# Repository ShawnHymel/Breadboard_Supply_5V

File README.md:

Breadboard Supply 5V
====================

PCB design files for Custom PCB with EAGLE workshop. 

License Information
-------------------

Please review the LICENSE.md file for license information. 

Distributed as-is; no warranty is given.

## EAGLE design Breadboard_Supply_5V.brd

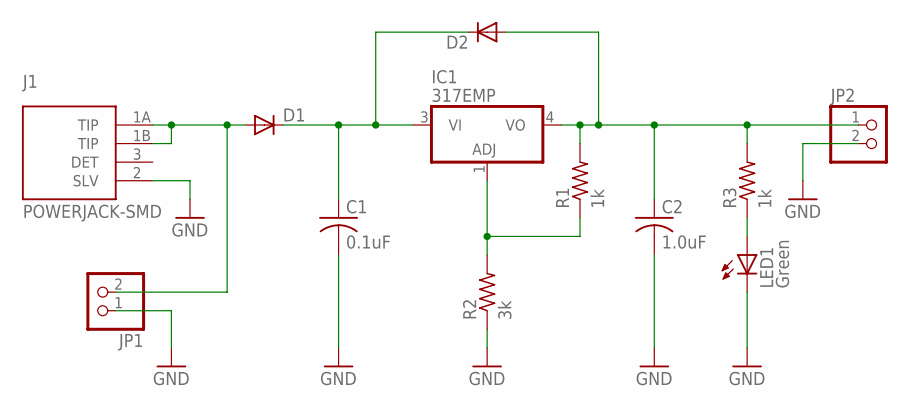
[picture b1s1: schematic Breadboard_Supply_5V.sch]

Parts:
C1: 0.1uF; C0805
C2: 1.0uF; C0805
D1, D2: DIODE-SMB; SMB
IC1: 317EMP; SOT223
J1: POWERJACK-SMD; PJ-002AH-SMT
JP1, JP2: PINHD-1X2; 1X02
LED1: Green; CHIPLED_0805
R1, R3: 1k; R0805
R2: 3k; R0805

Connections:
GND: C1.2, C2.2, J1.2 (SLV), JP1.1, JP2.2, LED1.C, R2.1
unnamed: D1.A, J1.1A (TIP), J1.1B (TIP), JP1.2
unnamed: C1.1, D1.C, D2.C, IC1.3 (VI)
unnamed: IC1.1 (ADJ), R1.1, R2.2
unnamed: C2.1, D2.A, IC1.4 (VO), JP2.1, R1.2, R3.2
unnamed: LED1.A, R3.1

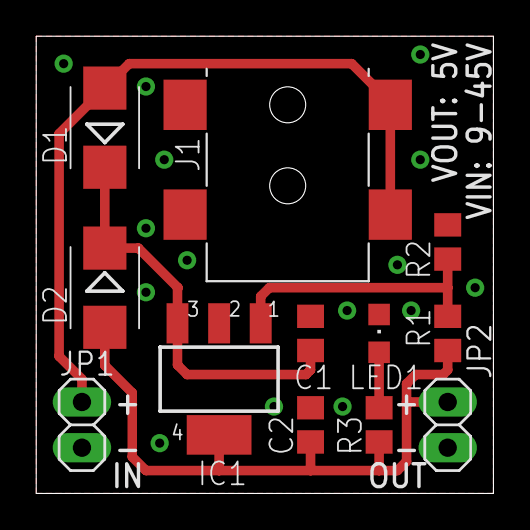
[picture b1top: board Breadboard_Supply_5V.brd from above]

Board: 2 copper layers, 25.4 x 25.4 mm, 12 parts (0 on the bottom side), 6 nets.

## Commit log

2015-09-15 Added BOM, README, and license.
2015-09-15 Added library
